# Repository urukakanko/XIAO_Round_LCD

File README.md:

# ラウンド液晶モジュール for XIAO RP2040（組立キット）

写真は作例です

XIAO RP2040を使用して1.28インチ240ｘ240ドットの円形液晶を駆動する基板モジュールのキットです。

(XIAOシリーズでは、XIAO ESP32C3 や　nRF52840で液晶表示が出来る事を確認しています)

(なお、XIAO ESP32S3を実装する場合には懸念事項があります。以下ページで説明していますのでご参照下さい。)

https://github.com/urukakanko/XIAO_square_lcd

この製品はキットですので、ご自分で同梱の部品をハンダ付けしてください。

円形液晶の裏にXIAOを配置することで、とても小さくスリムな形状になりました。

円形液晶にはGC9A01というコントローラーが使用されていますが、対応したグラフィックライブラリが数種類公開されています。

本モジュールは「自分でSMT部品が実装できたり、グラフィックライブラリの使い方を理解して液晶モジュールを駆動出来る人」をターゲットにしております。

# 形状および回路図

以下に外形イメージを示します

以下に回路図を示します

# ピンアサイン

M5Stamp とLCDの制御信号とのピン接続は以下となります。

注意；IO番号はRP2040用です　ESP32C2では異なります

- SCLK:IO2/D8
- MOSI:IO3/D10
- DC:IO26/D0
- CS:IO1/D7
- RST:IO27/D1
- バックライト:IO28/D2　バックライトLEDのPIN設定は必ず行ってください。未設定だと端子がハイインピーダンスとなりバックライトが不安定になります。

基板上にタクトスイッチを１個実装しています

- SWポート：IO0/D6

また、I2C接続を想定したGROVEコネクタがあります

- 1PIN : SCL  IO7/D5　(I/F電圧レベルは3.3V)
- 2PIN : SDA  IO8/D4　(I/F電圧レベルは3.3V）
- 3PIN : VCC（5Vか3.3Vを選択可能）
- 4PIN : GND 

さらに小型FETを搭載すると、小型のバイブレーターなどアクチェータ１個を駆動する事が可能です

（こちらはについては扱い方次第で不具合も発生しますので、回路を読み解き自己責任で部品調達、実装してください）

- 制御ポート：IO4/D9

# 部品実装について

部品の実装（ハンダ付け方法）などについては、以下資料をご確認ください

https://github.com/urukakanko/XIAO_Round_LCD/blob/main/%E9%83%A8%E5%93%81%E5%AE%9F%E8%A3%85%E3%81%AE%E8%AA%AC%E6%98%8E.pdf

# 使用するツールやライブラリ

XIAO RP2040のArduinoやPythonの導入については以下をご確認ください

https://wiki.seeedstudio.com/XIAO-RP2040/

グラフィックライブラリについてはlovyan様のLovyanGFXにて動作確認をしています

https://github.com/lovyan03/LovyanGFX

他、GC9A01に対応したライブラリが使用可能と考えています。

なお、RP2040とGC9A01の組合せにてcircuit pythonでも動作する事を確認しています

# サンプルソース

LovyanGFXのスケッチの例より引用させて頂きました。

サンプルその１

https://github.com/urukakanko/XIAO_Round_LCD/tree/main/xiao2040_round_lcd_MeterSample

サンプルその２

https://github.com/urukakanko/XIAO_Round_LCD/tree/main/xiao2040_round_lcd_PartyParrot

サンプルその３

https://github.com/urukakanko/XIAO_Round_LCD/tree/main/xiao2040_round_clockSample

# そーたメイ様のつくるっちに対応して頂きました

ファームウェアは以下です

https://github.com/sohtamei/TuKuRutch.ext/blob/master/libraries/lovyanGFXpico/src/src.ino.uf2

ファームウェアを書込んでから、Cromeブラウザで以下にアクセスします　簡単なデモプログラムです「set config」ブロックにてROUNDXIAOを選択して下さい

https://sohta02.sakura.ne.jp/tukurutch/#000000531

# 表示例

# Shigezone様にて販売中です

https://www.shigezone.com/product/roundlcd1_28/?fbclid=IwAR3sltDdaBDT0KiREBcUj3ycjUr6qAAMGzQqQChrtsmQ8KoZGPFba8SgSaQ

# 製作者

ウルカテクノロジー
Hiroyuki Sunagawa

https://www.facebook.com/URUKA-Technologies-105478404379918

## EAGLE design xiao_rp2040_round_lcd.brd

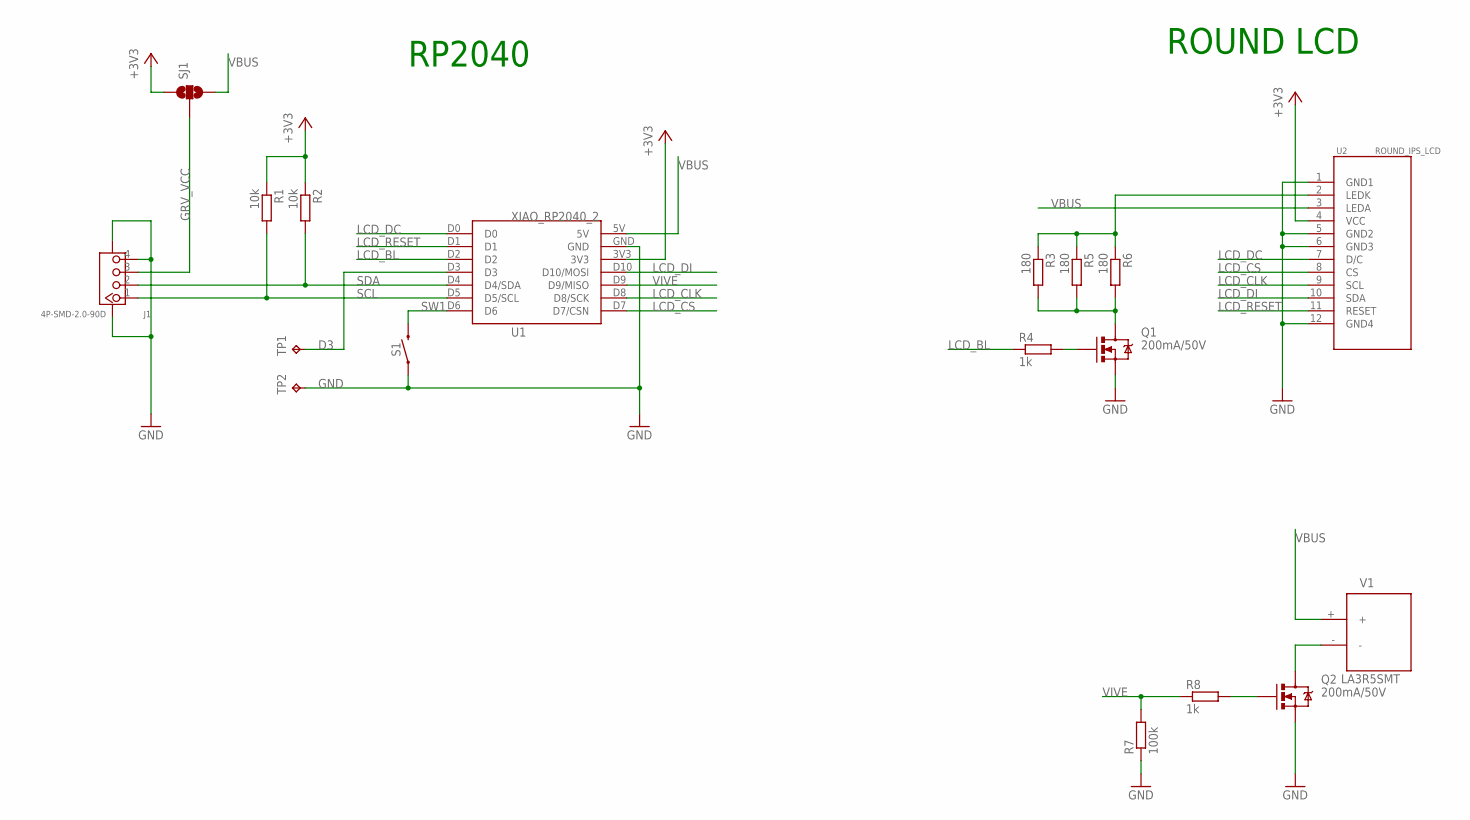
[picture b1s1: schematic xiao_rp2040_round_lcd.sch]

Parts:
J1: 4P-SMD-2.0-90D; HW4-SMD-2.0-90D
Q1, Q2: 200mA/50V; SOT23-3
R1, R2: 10k; R0603
R3, R5, R6: 180; R0603
R4, R8: 1k; R0603
R7: 100k; R0603
S1: TACT_SW_3X4; TACTILE_SWITCH_SMD_3X4MM
SJ1: SOLDERJUMPER_2WAYS; SJ_3
TP1, TP2: TPTP18R; TP18R
U1: XIAO_RP2040_2
U2: ROUND_IPS_LCD
V1: LA3R5SMT; LA3R5-2

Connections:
+3V3: R1.1, R2.1, SJ1.1, U1.3V3, U2.4 (VCC)
D3: TP1.TP, U1.D3
GND: J1.4, J1.SS1, J1.SS2, Q1.2 (S), Q2.2 (S), R7.1, S1.1, S1.2 (1), TP2.TP, U1.GND, U2.1 (GND1), U2.5 (GND2), U2.6 (GND3), U2.12 (GND4)
GRV_VCC: J1.3, SJ1.2
LCD_BL: R4.1, U1.D2
LCD_CLK: U1.D8 (D8/SCK), U2.9 (SCL)
LCD_CS: U1.D7 (D7/CSN), U2.8 (CS)
LCD_DC: U1.D0, U2.7 (D/C)
LCD_DI: U1.D10 (D10/MOSI), U2.10 (SDA)
LCD_RESET: U1.D1, U2.11 (RESET)
LED_K: R3.1, R5.1, R6.1, U2.2 (LEDK)
unnamed: Q1.1 (G), R4.2
unnamed: Q1.3 (D), R3.2, R5.2, R6.2
unnamed: Q2.3 (D), V1.-
unnamed: Q2.1 (G), R8.2
SCL: J1.1, R1.2, U1.D5 (D5/SCL)
SDA: J1.2, R2.2, U1.D4 (D4/SDA)
SW1: S1.3 (2), S1.4 (2), U1.D6
VBUS: SJ1.3, U1.5V, U2.3 (LEDA), V1.+
VIVE: R7.2, R8.1, U1.D9 (D9/MISO)

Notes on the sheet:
RP2040
ROUND LCD

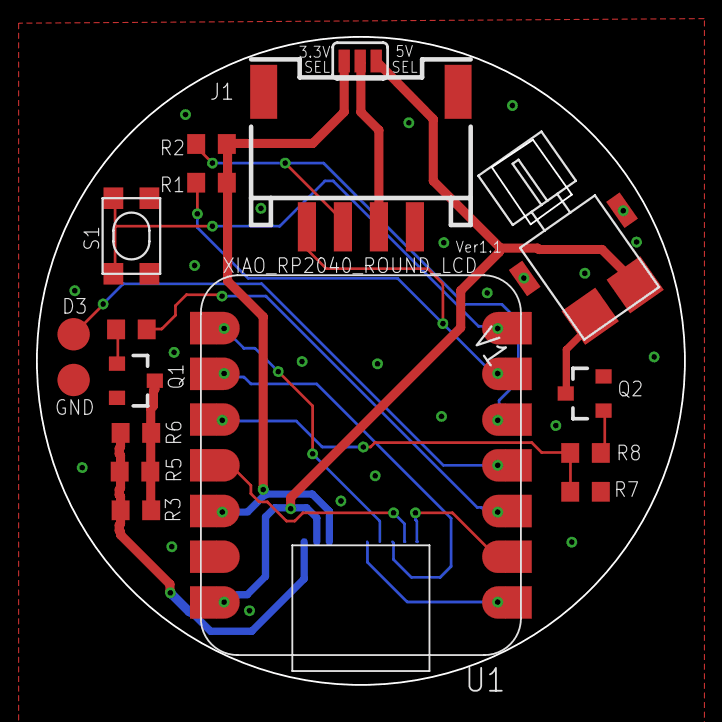
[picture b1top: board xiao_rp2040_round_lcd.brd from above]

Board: 2 copper layers, 36.0 x 36.0 mm, 18 parts (1 on the bottom side), 20 nets.

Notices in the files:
parts and their libraries:
SparkFun-Retired: Licensing:Creative Commons ShareAlike 4.0 International - https://creativecommons.org/licenses/by-sa/4.0
